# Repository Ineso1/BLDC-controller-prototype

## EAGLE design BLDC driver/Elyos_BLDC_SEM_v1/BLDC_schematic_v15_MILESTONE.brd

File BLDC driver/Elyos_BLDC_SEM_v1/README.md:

# Schematics and boards design evolution Folder
This folder contains the schematics and boards designs made until the final working version which is tagged as v17_FINAL

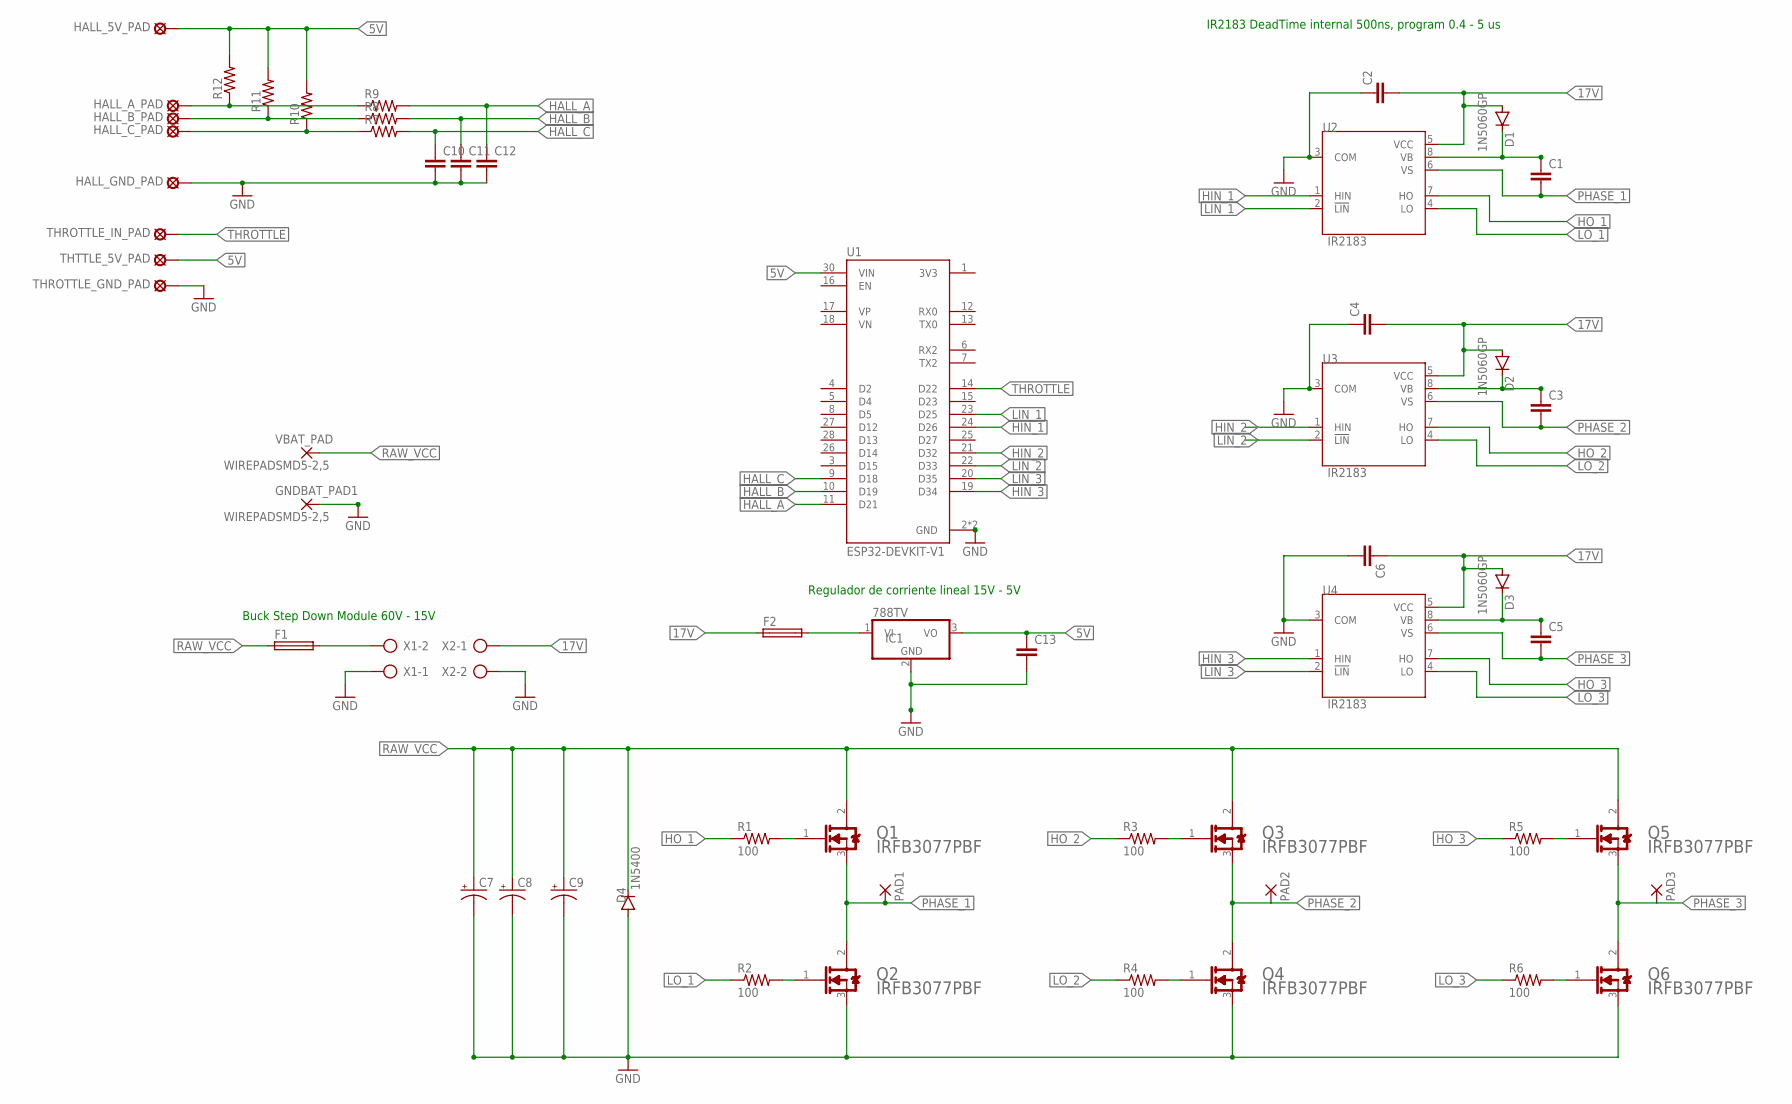
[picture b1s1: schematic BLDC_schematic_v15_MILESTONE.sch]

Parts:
C1, C2, C3, C4, C5, C6, C10, C11, C12, C13: C-EU025-030X050; C025-030X050
C7, C8, C9: CPOL-USTT5D11; TT5D11
D1, D2, D3: 1N5060GP; DO15-12
D4: 1N5400; DO201-15
F1, F2: SH22,5
GNDBAT_PAD1: WIREPADSMD5-2,5; 5-2,5
HALL_5V_PAD: MCS08
HALL_A_PAD: MCS08
HALL_B_PAD: MCS08
HALL_C_PAD: MCS08
HALL_GND_PAD: MCS08
IC1: 788TV; TO220V
PAD1, PAD2, PAD3: SMD5; SMD2,54-5,08
Q1, Q2, Q3, Q4, Q5, Q6: INFINEON_IRFB3077PBFINFINEON_IRFB3077PBF_0_0; INFINEON_IRFB3077PBF_0
R1, R2, R3, R4, R5, R6: 100; 0207/10
R7, R8, R9, R10, R11, R12: R-US_0204/7; 0204/7
THROTTLE_GND_PAD: MCS08
THROTTLE_IN_PAD: MCS08
THTTLE_5V_PAD: MCS08
U1: ESP32-DEVKIT-V1; MODULE_ESP32_DEVKIT_V1
U2, U3, U4: IR2183; DIP762W45P254L1092H533Q8
VBAT_PAD: WIREPADSMD5-2,5; 5-2,5
X1, X2: AK500/2-H

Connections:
5V: C13.1, HALL_5V_PAD.MP, IC1.3 (VO), R10.2, R11.2, R12.2, THTTLE_5V_PAD.MP, U1.30 (VIN)
17V: C2.2, C4.2, C6.1, D1.A, D2.A, D3.A, F2.1, U2.5 (VCC), U3.5 (VCC), U4.5 (VCC), X2.1
GND: C2.1, C4.1, C6.2, C7.-, C8.-, C9.-, C10.2, C11.2, C12.2, C13.2, D4.A, GNDBAT_PAD1.1, HALL_GND_PAD.MP, IC1.2 (GND), Q2.3 (S), Q4.3 (S), Q6.3 (S), THROTTLE_GND_PAD.MP, U1.2 (GND), U1.29 (GND), U2.3 (COM), U3.3 (COM), U4.3 (COM), X1.1, X2.2
HALL_A: C12.1, R9.2, U1.11 (D21)
HALL_B: C11.1, R8.2, U1.10 (D19)
HALL_C: C10.1, R7.2, U1.9 (D18)
HIN_1: U1.24 (D26), U2.1 (HIN)
HIN_2: U1.21 (D32), U3.1 (HIN)
HIN_3: U1.19 (D34), U4.1 (HIN)
HO_1: R1.1, U2.7 (HO)
HO_2: R3.1, U3.7 (HO)
HO_3: R5.1, U4.7 (HO)
LIN_1: U1.23 (D25), U2.2 (!LIN)
LIN_2: U1.22 (D33), U3.2 (!LIN)
LIN_3: U1.20 (D35), U4.2 (!LIN)
LO_1: R2.1, U2.4 (LO)
LO_2: R4.1, U3.4 (LO)
LO_3: R6.1, U4.4 (LO)
unnamed: C3.1, D2.C, U3.8 (VB)
unnamed: C5.1, D3.C, U4.8 (VB)
unnamed: C1.1, D1.C, U2.8 (VB)
unnamed: F1.2, X1.2
unnamed: Q3.1 (G), R3.2
unnamed: Q1.1 (G), R1.2
unnamed: Q2.1 (G), R2.2
unnamed: Q4.1 (G), R4.2
unnamed: Q5.1 (G), R5.2
unnamed: Q6.1 (G), R6.2
unnamed: F2.2, IC1.1 (VI)
unnamed: HALL_A_PAD.MP, R9.1, R12.1
unnamed: HALL_B_PAD.MP, R8.1, R11.1
unnamed: HALL_C_PAD.MP, R7.1, R10.1
PHASE_1: C1.2, PAD1.1, Q1.3 (S), Q2.2 (D), U2.6 (VS)
PHASE_2: C3.2, PAD2.1, Q3.3 (S), Q4.2 (D), U3.6 (VS)
PHASE_3: C5.2, PAD3.1, Q5.3 (S), Q6.2 (D), U4.6 (VS)
RAW_VCC: C7.+, C8.+, C9.+, D4.C, F1.1, Q1.2 (D), Q3.2 (D), Q5.2 (D), VBAT_PAD.1
THROTTLE: THROTTLE_IN_PAD.MP, U1.14 (D22)

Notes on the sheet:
IR2183 DeadTime internal 500ns, program 0.4 - 5 us
Buck Step Down Module 60V - 15V
Regulador de corriente lineal 15V - 5V

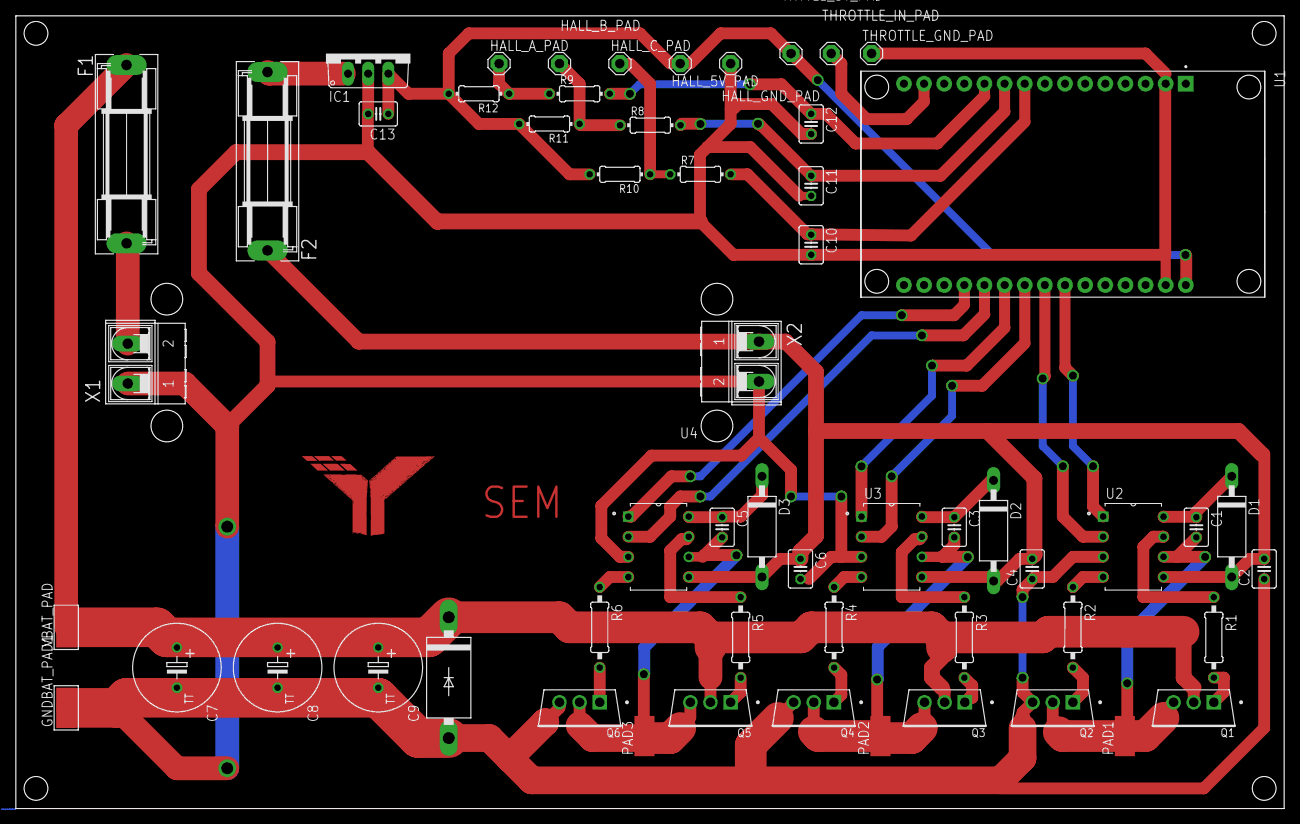
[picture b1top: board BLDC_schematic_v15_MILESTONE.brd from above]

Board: 2 copper layers, 160.0 x 100.0 mm, 57 parts (0 on the bottom side), 37 nets.

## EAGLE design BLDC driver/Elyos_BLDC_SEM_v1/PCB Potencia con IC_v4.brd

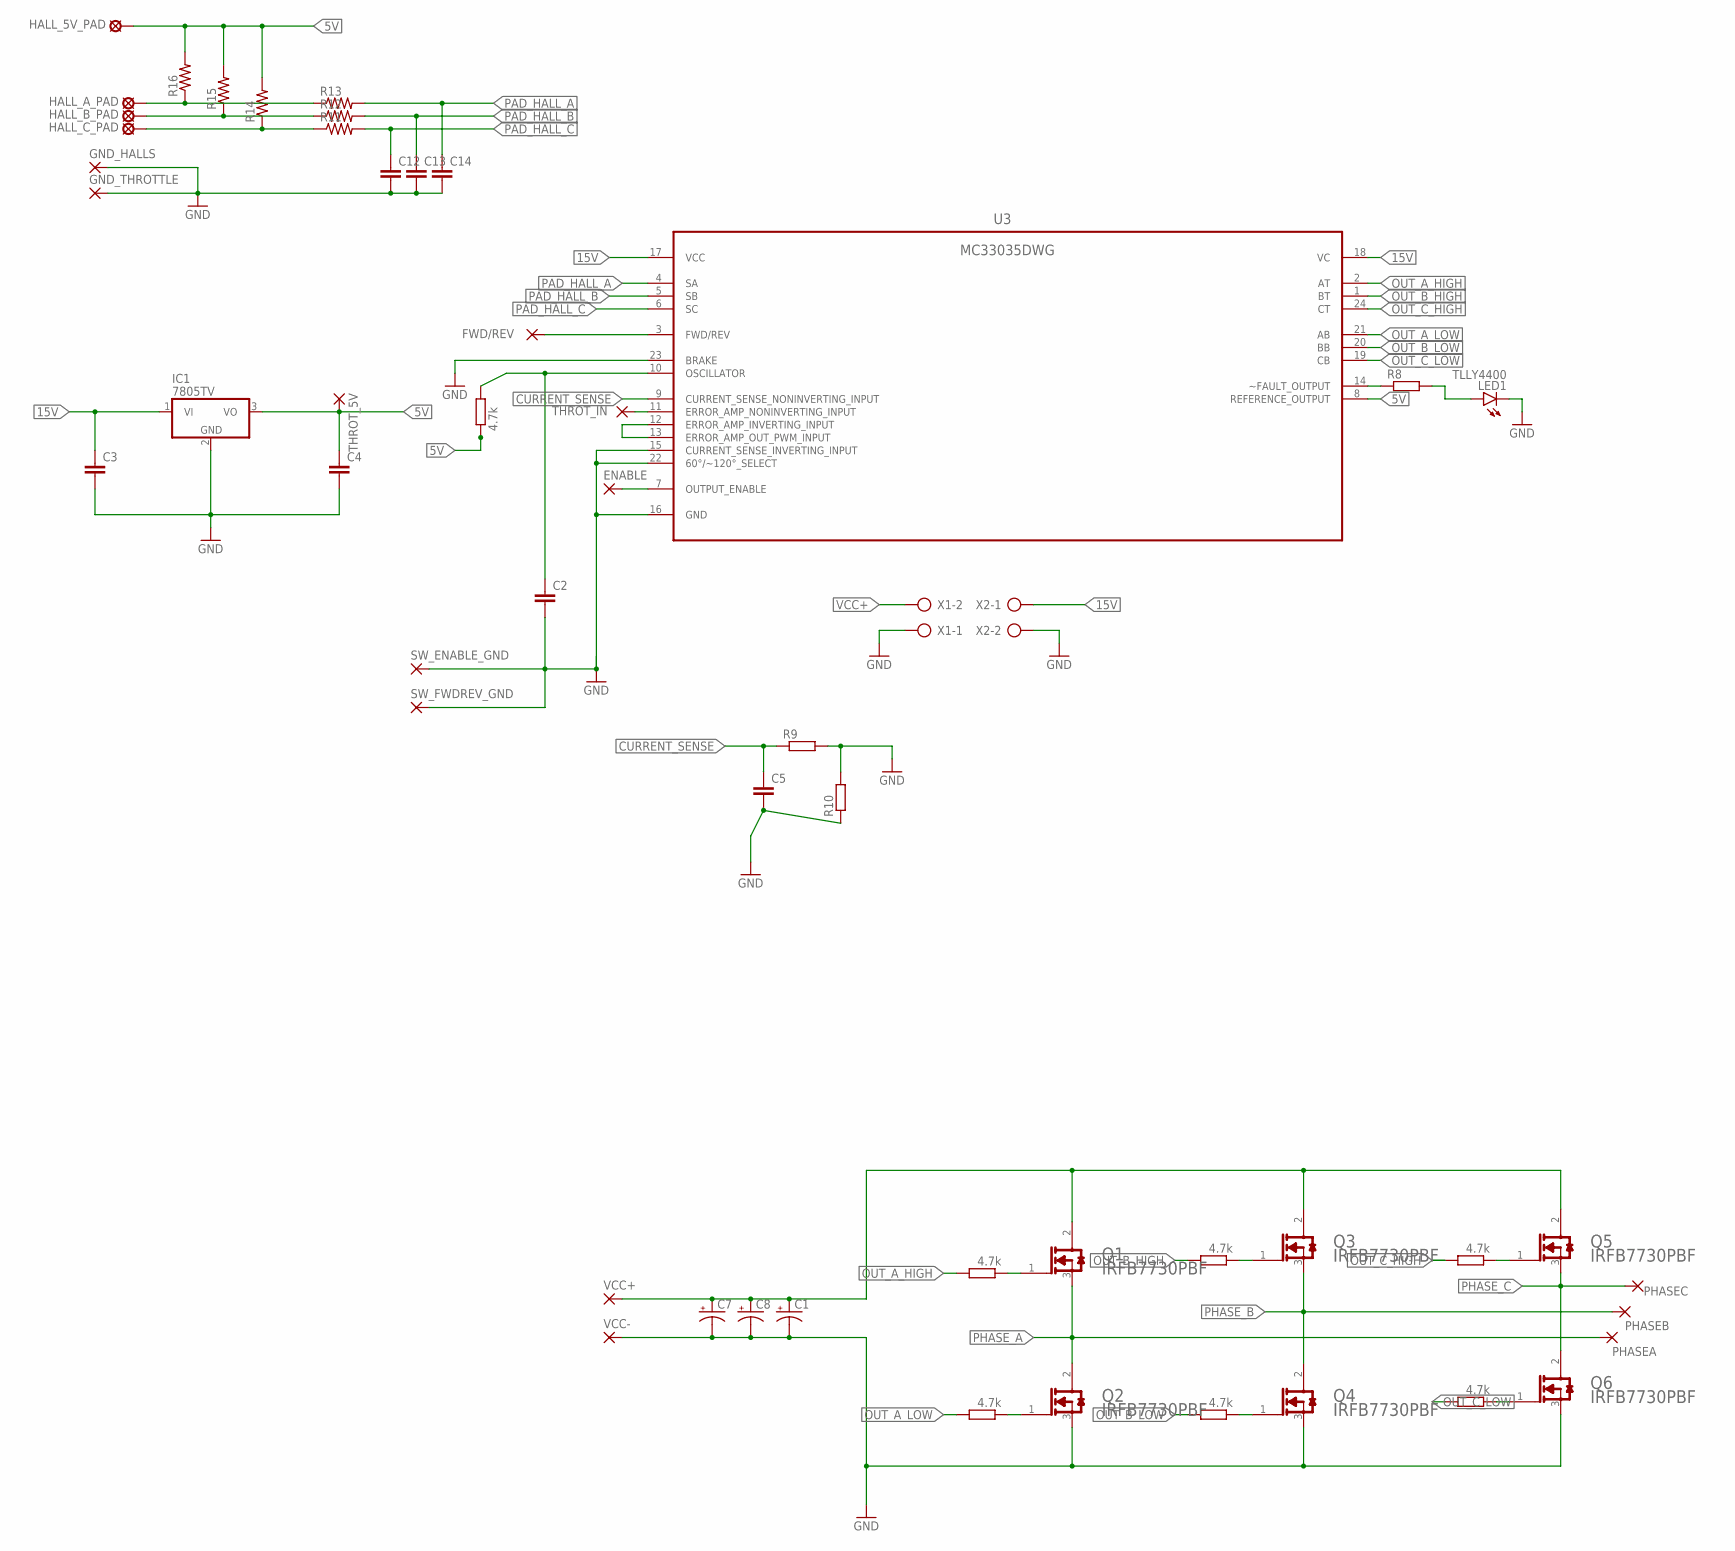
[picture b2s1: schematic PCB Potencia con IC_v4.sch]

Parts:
C1, C7, C8: CPOL-USTT5D11; TT5D11
C2, C3, C4, C5, C12, C13, C14: C-EU025-030X050; C025-030X050
ENABLE: 3,81/1,1
FWD/REV: 3,81/1,4
GND_HALLS: 3,81/1,1
GND_THROTTLE: 3,81/1,1
HALL_5V_PAD: MCS08
HALL_A_PAD: MCS08
HALL_B_PAD: MCS08
HALL_C_PAD: MCS08
IC1: 7805TV; TO220V
LED1: TLLY4400; LED3MM
PHASEA: 3,81/1,4
PHASEB: 3,81/1,4
PHASEC: 3,81/1,4
Q1, Q2, Q3, Q4, Q5, Q6: INFINEON_IRFB7730PBFINFINEON_IRFB7730PBF_0_0; INFINEON_IRFB7730PBF_0
R1, R2, R3, R4, R5, R6, R7: 4.7k; 0207/10
R8, R9, R10: R-EU_0207/10; 0207/10
R11, R12, R13, R14, R15, R16: R-US_0204/7; 0204/7
SW_ENABLE_GND: 3,81/1,4
SW_FWDREV_GND: 3,81/1,4
THROT_5V: 3,81/1,4
THROT_IN: 3,81/1,4
U3: MC33035DWG; SOIC127P1030X265-24N
VCC+: 3,81/1,4
VCC-: 3,81/1,4
X1, X2: AK500/2-H

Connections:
5V: C4.1, HALL_5V_PAD.MP, IC1.3 (VO), R7.1, R14.2, R15.2, R16.2, THROT_5V.1, U3.8 (REFERENCE_OUTPUT)
15V: U3.17 (VCC), U3.18 (VC), X2.1
CURRENT_SENSE: U3.9 (CURRENT_SENSE_NONINVERTING_INPUT)
GND: C1.-, C2.2, C3.2, C4.2, C5.2, C7.-, C8.-, C12.2, C13.2, C14.2, GND_HALLS.1, GND_THROTTLE.1, IC1.2 (GND), LED1.K (C), Q2.3 (S), Q4.3 (S), Q6.3 (S), R9.2, R10.1, R10.2, SW_ENABLE_GND.1, SW_FWDREV_GND.1, U3.15 (CURRENT_SENSE_INVERTING_INPUT), U3.16 (GND), U3.22 (60°/~120°_SELECT), U3.23 (BRAKE), VCC-.1, X1.1, X2.2
unnamed: C1.+, C7.+, C8.+, Q1.2 (D), Q3.2 (D), Q5.2 (D), VCC+.1
unnamed: Q1.1 (G), R1.1
unnamed: FWD/REV.1, U3.3 (FWD/REV)
unnamed: ENABLE.1, U3.7 (OUTPUT_ENABLE)
unnamed: Q2.1 (G), R2.1
unnamed: Q3.1 (G), R3.1
unnamed: Q4.1 (G), R4.1
unnamed: Q5.1 (G), R5.1
unnamed: Q6.1 (G), R6.1
unnamed: U3.12 (ERROR_AMP_INVERTING_INPUT), U3.13 (ERROR_AMP_OUT_PWM_INPUT)
unnamed: C3.1, IC1.1 (VI)
unnamed: R8.1, U3.14 (~FAULT_OUTPUT)
unnamed: THROT_IN.1, U3.11 (ERROR_AMP_NONINVERTING_INPUT)
unnamed: C2.1, R7.2, U3.10 (OSCILLATOR)
unnamed: LED1.A, R8.2
unnamed: C5.1, R9.1
unnamed: HALL_A_PAD.MP, R13.1, R16.1
unnamed: HALL_B_PAD.MP, R12.1, R15.1
unnamed: HALL_C_PAD.MP, R11.1, R14.1
OUT_A_HIGH: R1.2, U3.2 (AT)
OUT_A_LOW: R2.2, U3.21 (AB)
OUT_B_HIGH: R3.2, U3.1 (BT)
OUT_B_LOW: R4.2, U3.20 (BB)
OUT_C_HIGH: R5.2, U3.24 (CT)
OUT_C_LOW: R6.2, U3.19 (CB)
PAD_HALL_A: C14.1, R13.2, U3.4 (SA)
PAD_HALL_B: C13.1, R12.2, U3.5 (SB)
PAD_HALL_C: C12.1, R11.2, U3.6 (SC)
PHASE_A: PHASEA.1, Q1.3 (S), Q2.2 (D)
PHASE_B: PHASEB.1, Q3.3 (S), Q4.2 (D)
PHASE_C: PHASEC.1, Q5.3 (S), Q6.2 (D)
VCC+: X1.2

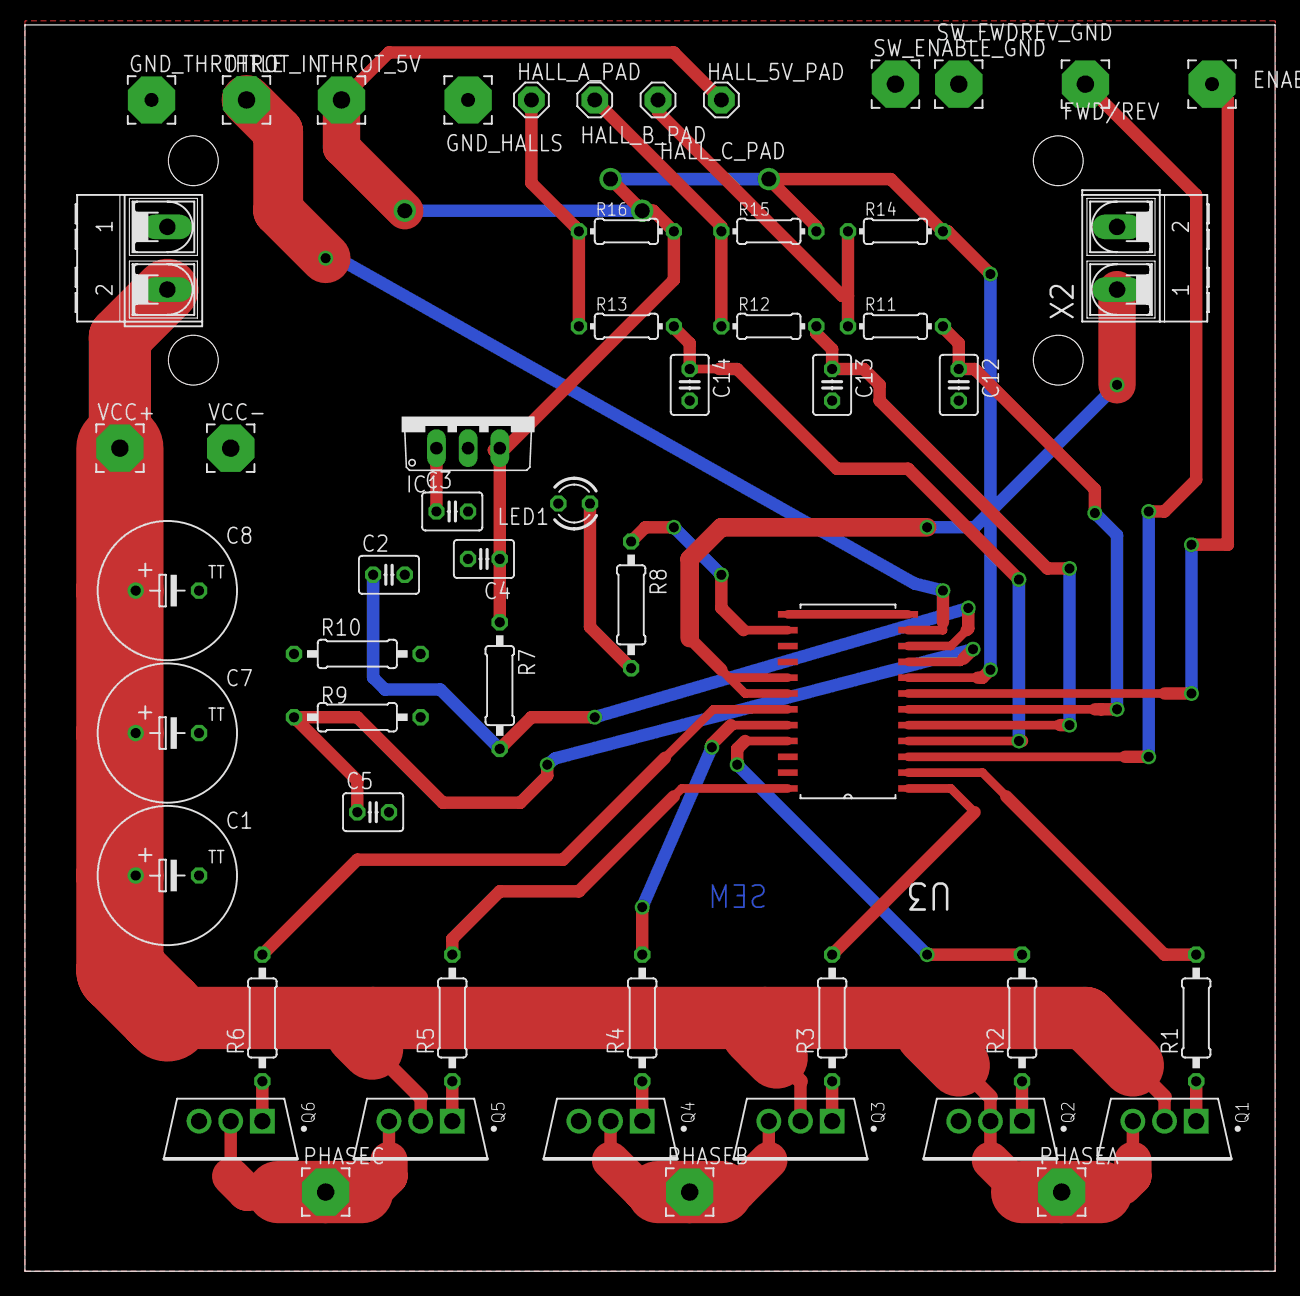
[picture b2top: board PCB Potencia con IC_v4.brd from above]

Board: 2 copper layers, 100.3 x 100.0 mm, 54 parts (0 on the bottom side), 34 nets.

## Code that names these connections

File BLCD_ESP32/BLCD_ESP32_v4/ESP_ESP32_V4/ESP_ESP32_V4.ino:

//Official Code 
/**********************************************

Project Name: BLDC controller
Author: Elyos team
Date: 2022-03-03
Microcontroller: ESP 32
Description: A BLDC controller version 3 

*************************************************/
 
 
 /*
  Pinout:
  - GPIO 21: Hall A
  - GPIO 19: Hall B
  - GPIO 13: Hall C
  - GPIO 27: Phase A PWM 
  - GPIO 32: Phase B PWM
  - GPIO 26: Phase C PWM
  - GPIO 12: Phase AA PWM
  - GPIO 33: Phase BB PWM
  - GPIO 26: Phase CC PWM
  - GPIO 4: Potenciometer pin (pedal pin)
 */

const int pot_pin = 4;              // Potentiometer pin
const float pwm_min = 0.0;           // Minimum PWM duty cycle
const float pwm_max = 255.0;         // Maximum PWM duty cycle
const float pwm_frequency = 2000;  // PWM frequency in Hz
const int num_comm_steps = 7;         // Number of commutation steps
const int hall_a_pin = 21;            // Hall sensor A pin
const int hall_b_pin = 19;            // Hall sensor B pin
const int hall_c_pin = 13;            // Hall sensor C pin

//PWM write pins
const int pwm_pin_c = 27;             // PWM pin for phase A //27
const int pwm_pin_b = 32;             // PWM pin for phase B
const int pwm_pin_a = 26;             // PWM pin for phase C //26

const int pwm_pin_cc = 12;             // PWM pin for phase A //12
const int pwm_pin_bb = 33;             // PWM pin for phase B
const int pwm_pin_aa = 25;             // PWM pin for phase C //25


int AH, AL, BH, BL, CH, CL;
float phase_a_duty, phase_b_duty, phase_c_duty;

/*
  Look up table for signal commutation

  Each row represents a step at the commutation sequence, each column represents a phase to write
*/
const int commutation_table[num_comm_steps][7] = {
  {0, 0, 2, 1, 0, 1},
  {2, 0, 0, 1, 0, 1},
  {2, 0, 0, 1, 1, 0},
  {0, 2, 0, 1, 1, 0},
  {0, 2, 0, 0, 1, 1},
  {0, 0, 2, 0, 1, 1},
  {0, 0, 0, 0, 0, 0}
};


void setup() {
  Serial.begin(9600);
  
  pinMode(hall_a_pin, INPUT);
  pinMode(hall_b_pin, INPUT);
  pinMode(hall_c_pin, INPUT);
  pinMode(pwm_pin_a, OUTPUT);
  pinMode(pwm_pin_b, OUTPUT);
  pinMode(pwm_pin_c, OUTPUT);

  //.....Fases prueba
  pinMode(pwm_pin_aa, OUTPUT);
  pinMode(pwm_pin_bb, OUTPUT);
  pinMode(pwm_pin_cc, OUTPUT);

  ledcSetup(0, pwm_frequency, 8);
  ledcSetup(1, pwm_frequency, 8);
  ledcSetup(2, pwm_frequency, 8);
  ledcAttachPin(pwm_pin_a, 0);
  ledcAttachPin(pwm_pin_b, 1);
  ledcAttachPin(pwm_pin_c, 2);
}

/*
  Hall sensors reading and state write process loop
*/

void loop() {
  int hall_a_val = !digitalRead(hall_a_pin);
  int hall_b_val = !digitalRead(hall_b_pin);
  int hall_c_val = !digitalRead(hall_c_pin);


  int hall_state = (hall_a_val << 2) | (hall_b_val << 1) | hall_c_val;
  int commutation_step = 0;
  switch (hall_state) {
    case 0b101:
      commutation_step = 1;
      break;
    case 0b001:
      commutation_step = 2;
      break;
    case 0b011:
      commutation_step = 3;
      break;
    case 0b010:
      commutation_step = 4;
      break;
    case 0b110:
      commutation_step = 5;
      break;
    case 0b100:
      commutation_step = 0;
      break;
    default:
      commutation_step = 6;
    break;
  }

/*
  Throttle pedal potetiometer analog signal mapping (pot_val) to an 8bit pwm duty cycle value (pwm_duty) 
  Resolution and ranges for potentiometers analog value: 12 bits, 0 - 4095
  Resolution and ranges for mapped duty cycle value: 8 bits, 0 - 255 
*/

  int pot_val = analogRead(pot_pin);
  float pwm_duty = map(pot_val, 80, 4095, pwm_min, pwm_max);

  /*if(pot_val < 60){
    commutation_step = 6;
  }*/

  AH = commutation_table[commutation_step][0];
  AL = commutation_table[commutation_step][3];
  BH = commutation_table[commutation_step][1];
  BL = commutation_table[commutation_step][4];
  CH = commutation_table[commutation_step][2];
  CL = commutation_table[commutation_step][5];

  int phase_a_duty = AH * pwm_duty /2;
  int phase_b_duty = BH * pwm_duty /2;
  int phase_c_duty = CH * pwm_duty /2;
  int phase_aa_duty = AL;
  int phase_bb_duty = BL;
  int phase_cc_duty = CL;


  ledcWrite(0, phase_a_duty);
  ledcWrite(1, phase_b_duty);
  ledcWrite(2, phase_c_duty);

  digitalWrite(pwm_pin_aa, phase_aa_duty);
  digitalWrite(pwm_pin_bb, phase_bb_duty);
  digitalWrite(pwm_pin_cc, phase_cc_duty);

  Serial.print(pot_val);
  Serial.print("\t--");
  Serial.print(pwm_duty);
  Serial.print("\t--");
  Serial.print(hall_c_val);
  Serial.print("\t---");
  Serial.print(hall_a_val);
  Serial.print(" - ");
  Serial.print(hall_b_val);
  Serial.print(" - ");
  Serial.print(hall_c_val);
  Serial.print("\t---");
    
  //Serial.println(hall_state, BIN);

  Serial.print("\t|||\t");
  Serial.print(phase_a_duty);
  Serial.print(" - ");
  Serial.print(phase_b_duty);
  Serial.print(" - ");
  Serial.print(phase_c_duty);

  //........Fases prueba
  Serial.print(" ---- ");
  Serial.print(phase_aa_duty);
  Serial.print(" - ");
  Serial.print(phase_bb_duty);
  Serial.print(" - ");
  Serial.println(phase_cc_duty);
  //delay(10);


}

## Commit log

2023-03-08 eagle project
2023-03-20 Actualizacion diseno controlador
2023-04-05 version
2023-04-06 conmutacion bien
2023-04-11 Codigo oficial BLDC_ESP32_v3
    Aumento de frecuencia
2023-04-12 ultima version
2023-04-12 Correccion
2023-04-12 acelerador thing
2023-04-12 throttle thing
2023-04-14 Carpeta con todas las placas agregada
2023-04-14 Board y esquematico final con readme
2023-04-20 actualizacion ocdigo
